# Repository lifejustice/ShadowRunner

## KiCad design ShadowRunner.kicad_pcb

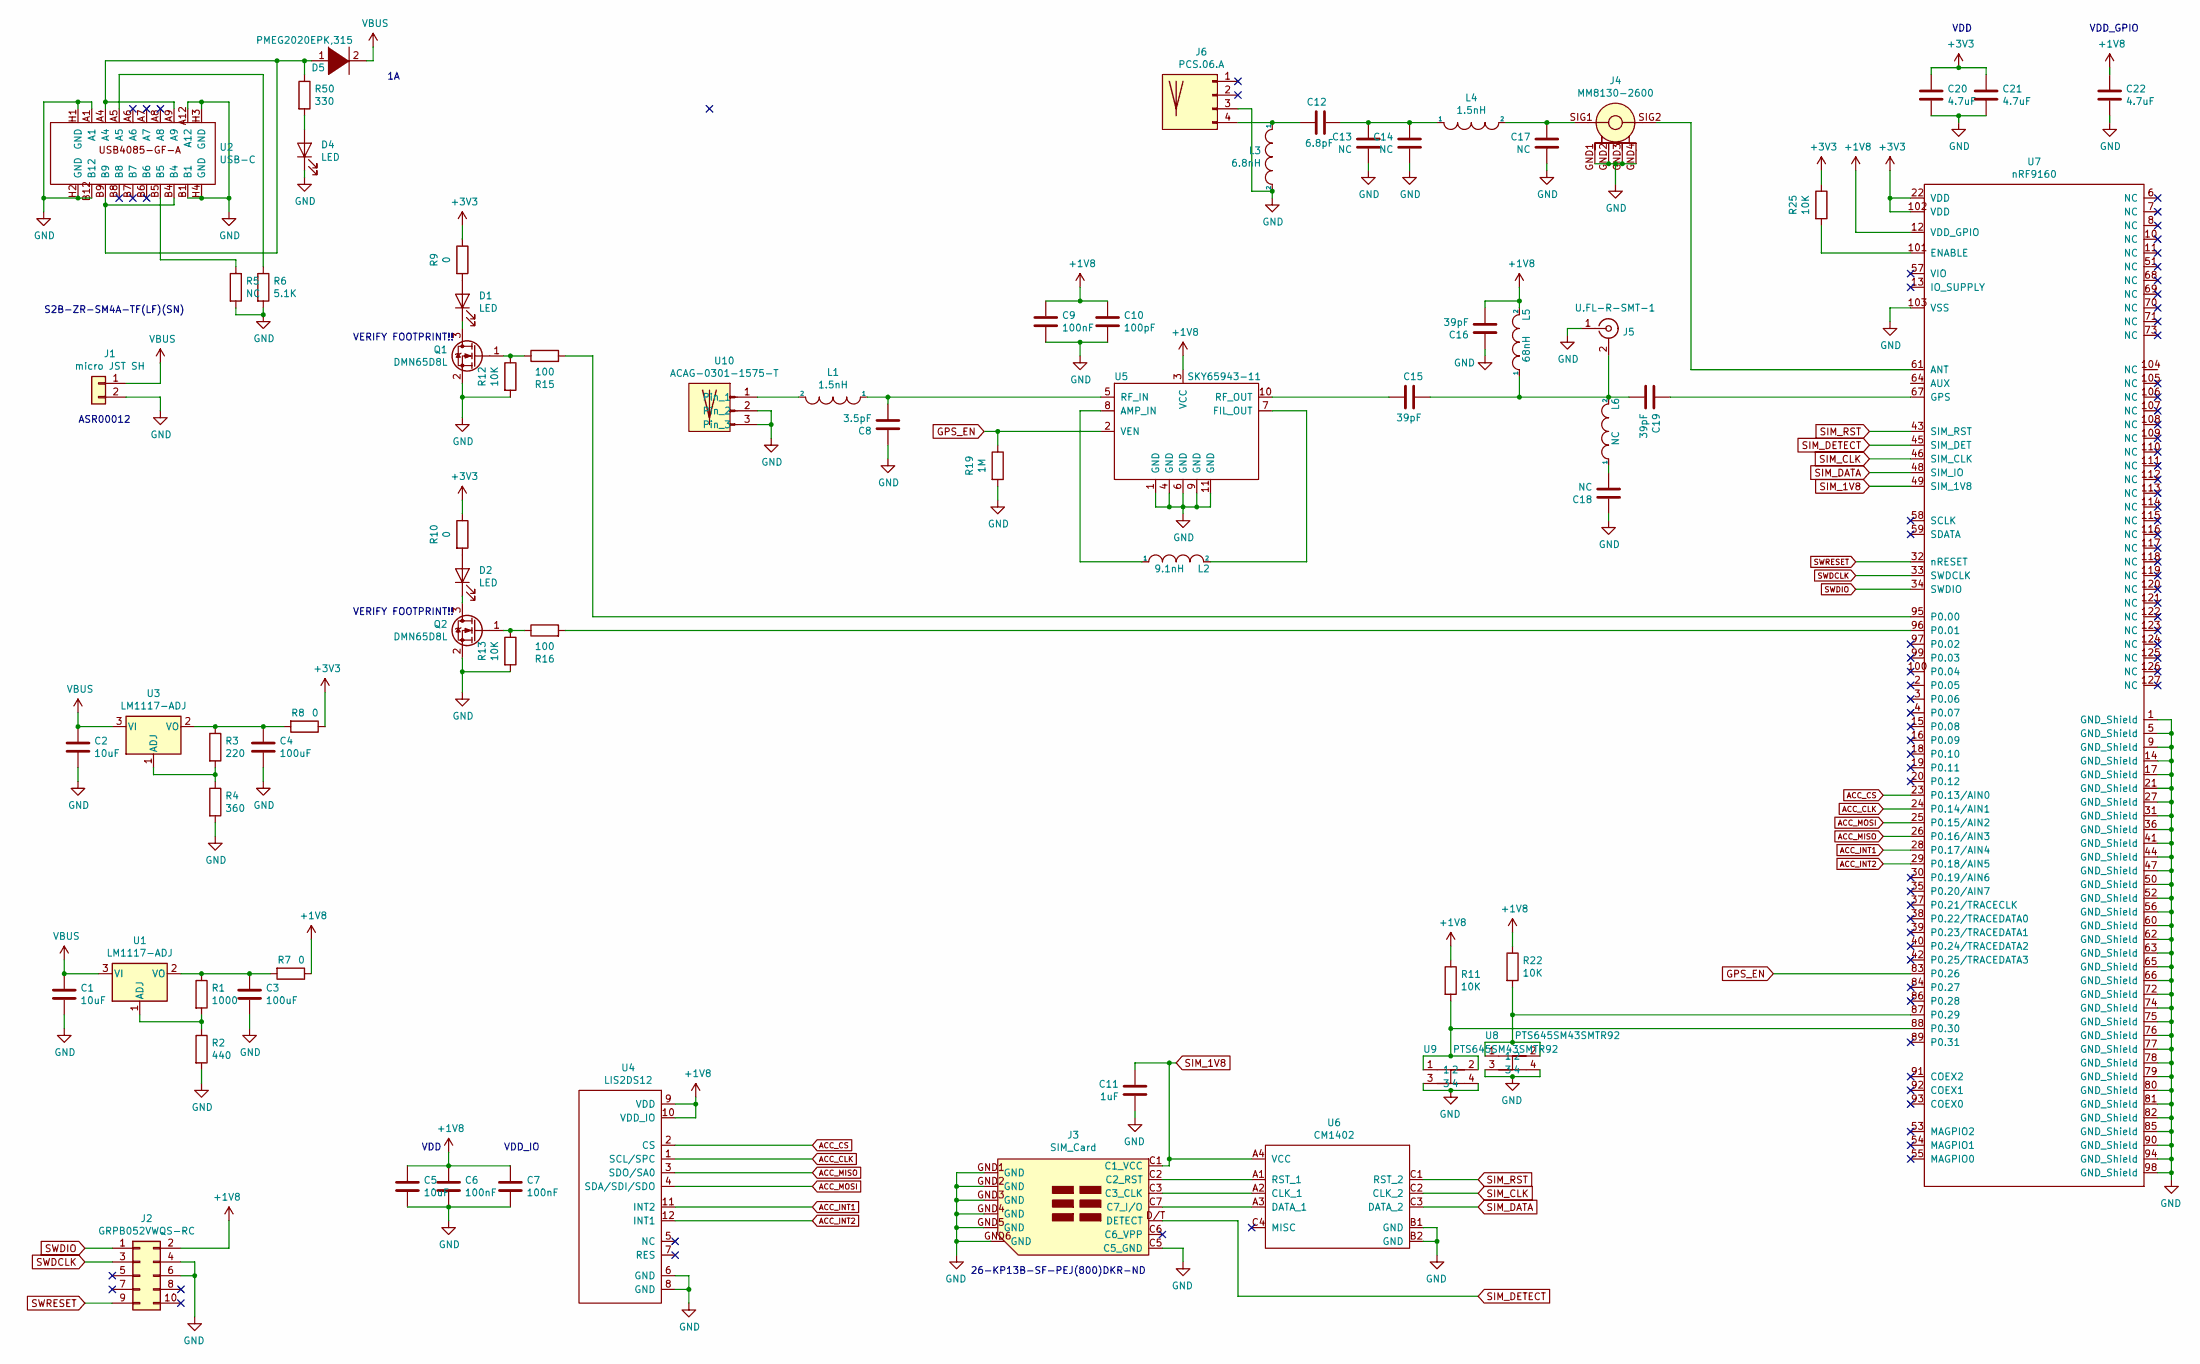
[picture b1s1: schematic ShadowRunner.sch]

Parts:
C1, C2, C5: 10uF; C_0402_1005Metric
C3, C4: 100uF; C_0805_2012Metric
C6, C7, C9: 100nF; C_0402_1005Metric
C8: 3.5pF; C_0402_1005Metric
C10: 100pF; C_0402_1005Metric
C11: 1uF; C_0402_1005Metric
C12: 6.8pF; C_0402_1005Metric
C13, C14, C17, C18: NC; C_0402_1005Metric
C15, C16, C19: 39pF; C_0402_1005Metric
C20, C21, C22: 4.7uF; C_0402_1005Metric
D1, D2, D4: LED; LED_0402_1005Metric
D5: PMEG2020EPK,315; D_0603_1608Metric_Pad1.05x0.95mm_HandSolder
J1: micro JST SH; S2B-ZR-SM4A-TFLFSN
J2: GRPB052VWQS-RC; PinHeader_2x05_P1.27mm_Vertical_SMD
J3: SIM_Card; 26-KP13B-SF-PEJ(800)DKR-ND
J4: MM8130-2600
J5: U.FL-R-SMT-1; U.FL-R-SMT-110
J6: PCS.06.A
L1, L4: 1.5nH; L_0402_1005Metric
L2: 9.1nH; L_0402_1005Metric
L3: 6.8nH; L_0402_1005Metric
L5: 68nH; L_0402_1005Metric
L6: NC; L_0402_1005Metric
Q1, Q2: DMN65D8L; SOT-23
R1: 1000; R_0402_1005Metric
R2: 440; R_0402_1005Metric
R3: 220; R_0402_1005Metric
R4: 360; R_0402_1005Metric
R5: NC; R_0402_1005Metric
R6: 5.1K; R_0402_1005Metric
R7, R8, R9, R10: 0; R_0402_1005Metric
R11, R12, R13, R22, R25: 10K; R_0402_1005Metric
R15, R16: 100; R_0402_1005Metric
R19: 1M; R_0402_1005Metric
R50: 330; R_0402_1005Metric
U1, U3: LM1117-ADJ; SOT-223
U2: USB-C; USB4085-GF-A
U4: LIS2DS12; LGA-12_2x2mm_P0.5mm
U5: SKY65943-11; SKY65943_11
U6: CM1402
U7: nRF9160
U8, U9: PTS645SM43SMTR92
U10: ACAG-0301-1575-T; ACAG0301-1575-T

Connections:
+1V8: C5.1, C6.1, C7.1, C9.1, C10.1, C16.2, C22.1, J2.2, L5.2, R7.1, R11.1, R22.1, U4.9 (VDD), U4.10 (VDD_IO), U5.3 (VCC), U7.12 (VDD_GPIO)
+3V3: C20.1, C21.1, R8.1, R9.1, R10.1, R25.1, U7.22 (VDD), U7.102 (VDD)
ACC_CLK: U4.1 (SCL/SPC), U7.24 (P0.14/AIN1)
ACC_CS: U4.2 (CS), U7.23 (P0.13/AIN0)
ACC_INT1: U4.11 (INT2), U7.28 (P0.17/AIN4)
ACC_INT2: U4.12 (INT1), U7.29 (P0.18/AIN5)
ACC_MISO: U4.3 (SDO/SA0), U7.26 (P0.16/AIN3)
ACC_MOSI: U4.4 (SDA/SDI/SDO), U7.25 (P0.15/AIN2)
GND: C1.2, C2.2, C3.2, C4.2, C5.2, C6.2, C7.2, C8.1, C9.2, C10.2, C11.2, C13.2, C14.2, C16.1, C17.2, C18.1, C20.2, C21.2, C22.2, D4.1 (K), J1.2, J2.4, J2.6, J3.C5 (C5_GND), J3.GND1 (GND), J3.GND2 (GND), J3.GND3 (GND), J3.GND4 (GND), J3.GND5 (GND), J3.GND6 (GND), J4.GND1 (GND), J4.GND2, J4.GND3, J4.GND4, J5.1 (In), J6.3, L3.2, Q1.2 (S), Q2.2 (S), R2.2, R4.2, R5.2, R6.2, R12.2, R13.2, R19.2, U2.A1, U2.A12, U2.B1, U2.B12, U2.H1 (GND), U2.H2 (GND), U2.H3 (GND), U2.H4 (GND), U4.6 (GND), U4.8 (GND), U5.1 (GND), U5.4 (GND), U5.6 (GND), U5.9 (GND), U5.11 (GND), U6.B1 (GND), U6.B2 (GND), U7.1 (GND_Shield), U7.5 (GND_Shield), U7.9 (GND_Shield), U7.14 (GND_Shield), U7.17 (GND_Shield), U7.21 (GND_Shield), U7.27 (GND_Shield), U7.31 (GND_Shield), U7.36 (GND_Shield), U7.41 (GND_Shield), U7.44 (GND_Shield), U7.47 (GND_Shield), U7.50 (GND_Shield), U7.52 (GND_Shield), U7.56 (GND_Shield), U7.60 (GND_Shield), U7.62 (GND_Shield), U7.63 (GND_Shield), U7.65 (GND_Shield), U7.66 (GND_Shield), U7.72 (GND_Shield), U7.74 (GND_Shield), U7.75 (GND_Shield), U7.76 (GND_Shield), U7.77 (GND_Shield), U7.78 (GND_Shield), U7.79 (GND_Shield), U7.80 (GND_Shield), U7.81 (GND_Shield), U7.82 (GND_Shield), U7.85 (GND_Shield), U7.90 (GND_Shield), U7.94 (GND_Shield), U7.98 (GND_Shield), U7.103 (VSS), U8.3, U8.4, U9.3, U9.4, U10.2, U10.3
GPS_EN: R19.1, U5.2 (VEN), U7.83 (P0.26)
unnamed: C3.1, R1.1, R7.2, U1.2 (VO)
unnamed: C4.1, R3.1, R8.2, U3.2 (VO)
unnamed: C8.2, L1.1, U5.5 (RF_IN)
unnamed: C12.1, J6.4, L3.1
unnamed: C12.2, C13.1, C14.1, L4.1
unnamed: C15.1, C19.2, J5.2 (Ext), L5.1, L6.2
unnamed: C15.2, U5.10 (RF_OUT)
unnamed: C17.1, J4.SIG1 (In), L4.2
unnamed: C18.2, L6.1
unnamed: C19.1, U7.67 (GPS)
unnamed: D1.1 (K), Q1.3 (D)
unnamed: D1.2 (A), R9.2
unnamed: D2.1 (K), Q2.3 (D)
unnamed: D2.2 (A), R10.2
unnamed: D4.2 (A), R50.2
unnamed: D5.1 (K), R50.1, U2.A4, U2.A9, U2.B4, U2.B9
unnamed: J3.C2 (C2_RST), U6.A1 (RST_1)
unnamed: J3.C3 (C3_CLK), U6.A2 (CLK_1)
unnamed: J3.C7 (C7_I/O), U6.A3 (DATA_1)
unnamed: J4.SIG2 (Out), U7.61 (ANT)
unnamed: L1.2, U10.1
unnamed: L2.1, U5.8 (AMP_IN)
unnamed: L2.2, U5.7 (FIL_OUT)
unnamed: Q1.1 (G), R12.1, R15.1
unnamed: Q2.1 (G), R13.1, R16.1
unnamed: R1.2, R2.1, U1.1 (ADJ)
unnamed: R3.2, R4.1, U3.1 (ADJ)
unnamed: R5.1, U2.B5
unnamed: R6.1, U2.A5
unnamed: R11.2, U7.88 (P0.30), U9.1, U9.2
unnamed: R15.2, U7.95 (P0.00)
unnamed: R16.2, U7.96 (P0.01)
unnamed: R22.2, U7.87 (P0.29), U8.1, U8.2
unnamed: R25.2, U7.101 (ENABLE)
SIM_1V8: C11.1, J3.C1 (C1_VCC), U6.A4 (VCC), U7.49 (SIM_1V8)
SIM_CLK: U6.C2 (CLK_2), U7.46 (SIM_CLK)
SIM_DATA: U6.C3 (DATA_2), U7.48 (SIM_IO)
SIM_DETECT: J3.D/T (DETECT), U7.45 (SIM_DET)
SIM_RST: U6.C1 (RST_2), U7.43 (SIM_RST)
SWDCLK: J2.3, U7.33 (SWDCLK)
SWDIO: J2.1, U7.34 (SWDIO)
SWRESET: J2.9, U7.32 (nRESET)
VBUS: C1.1, C2.1, D5.2 (A), J1.1, U1.3 (VI), U3.3 (VI)

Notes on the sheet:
VDD
VDD_IO
VDD_GPIO
26-KP13B-SF-PEJ(800)DKR-ND
VERIFY FOOTPRINT!!
S2B-ZR-SM4A-TF(LF)(SN)
ASR00012

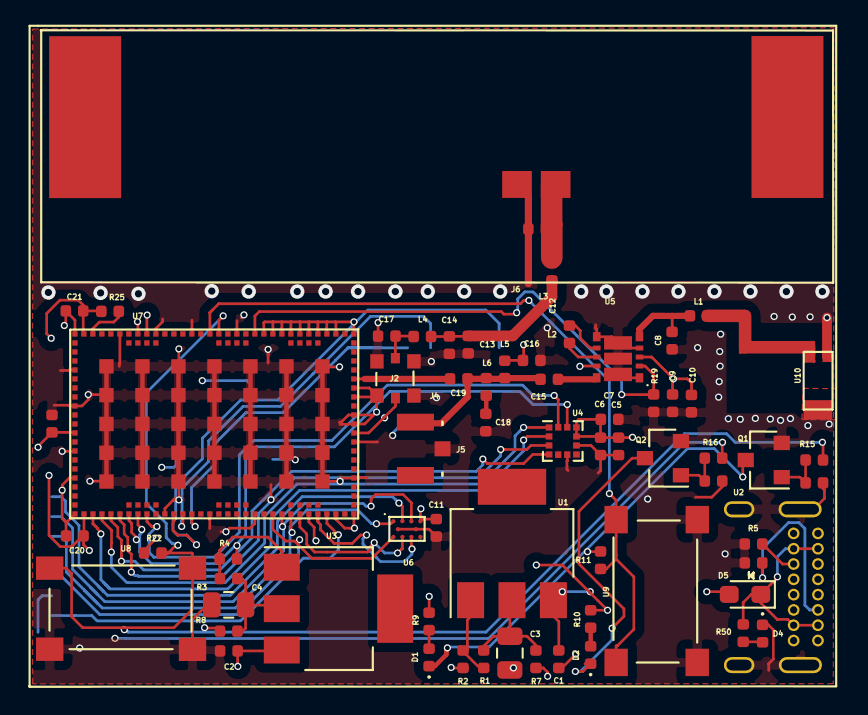
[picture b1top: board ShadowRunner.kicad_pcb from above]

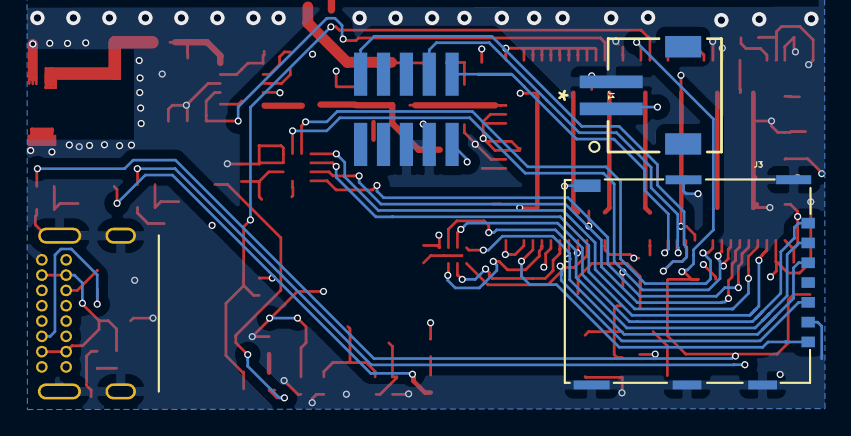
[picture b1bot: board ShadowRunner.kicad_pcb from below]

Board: 4 copper layers, 69 parts (4 on the bottom side), 53 nets.

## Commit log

2020-03-23 Initial Save
2020-03-23 Added RF Matching circuits
2020-03-23 Updated Schematic
    -Added power supplies
    -Added Battery
    -Added 3 buttons
    -Added 3 LEDs
2020-03-24 Creating netlist
2020-03-25 Making footprints
2020-03-27 Updating footprints.
2020-03-27 Created footprints, generated netlist
    Created footprints
    Generated netlist
2020-03-30 Working on footprint.
2020-03-30 Layout improved.
    Let's see if I'll be able to route this thing....
2020-03-30 lots of routing
2020-04-01 rerouting
2020-04-02 All connections made
2020-04-03 Final review
2020-04-04 Fixed capacitor footprints
2020-04-05 stuff

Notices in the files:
parts and their libraries:
Copyright 2016 Accelerated Designs. All rights reserved.
